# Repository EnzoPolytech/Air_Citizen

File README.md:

# Air_Citizen
Ressources concernant la conception d'un module de capteur de gaz pour le client Air Citizen dans la cadre du Projet Industriel de 4eme année d'EISE de l'école d'ingénieur Polytech Sorbonne

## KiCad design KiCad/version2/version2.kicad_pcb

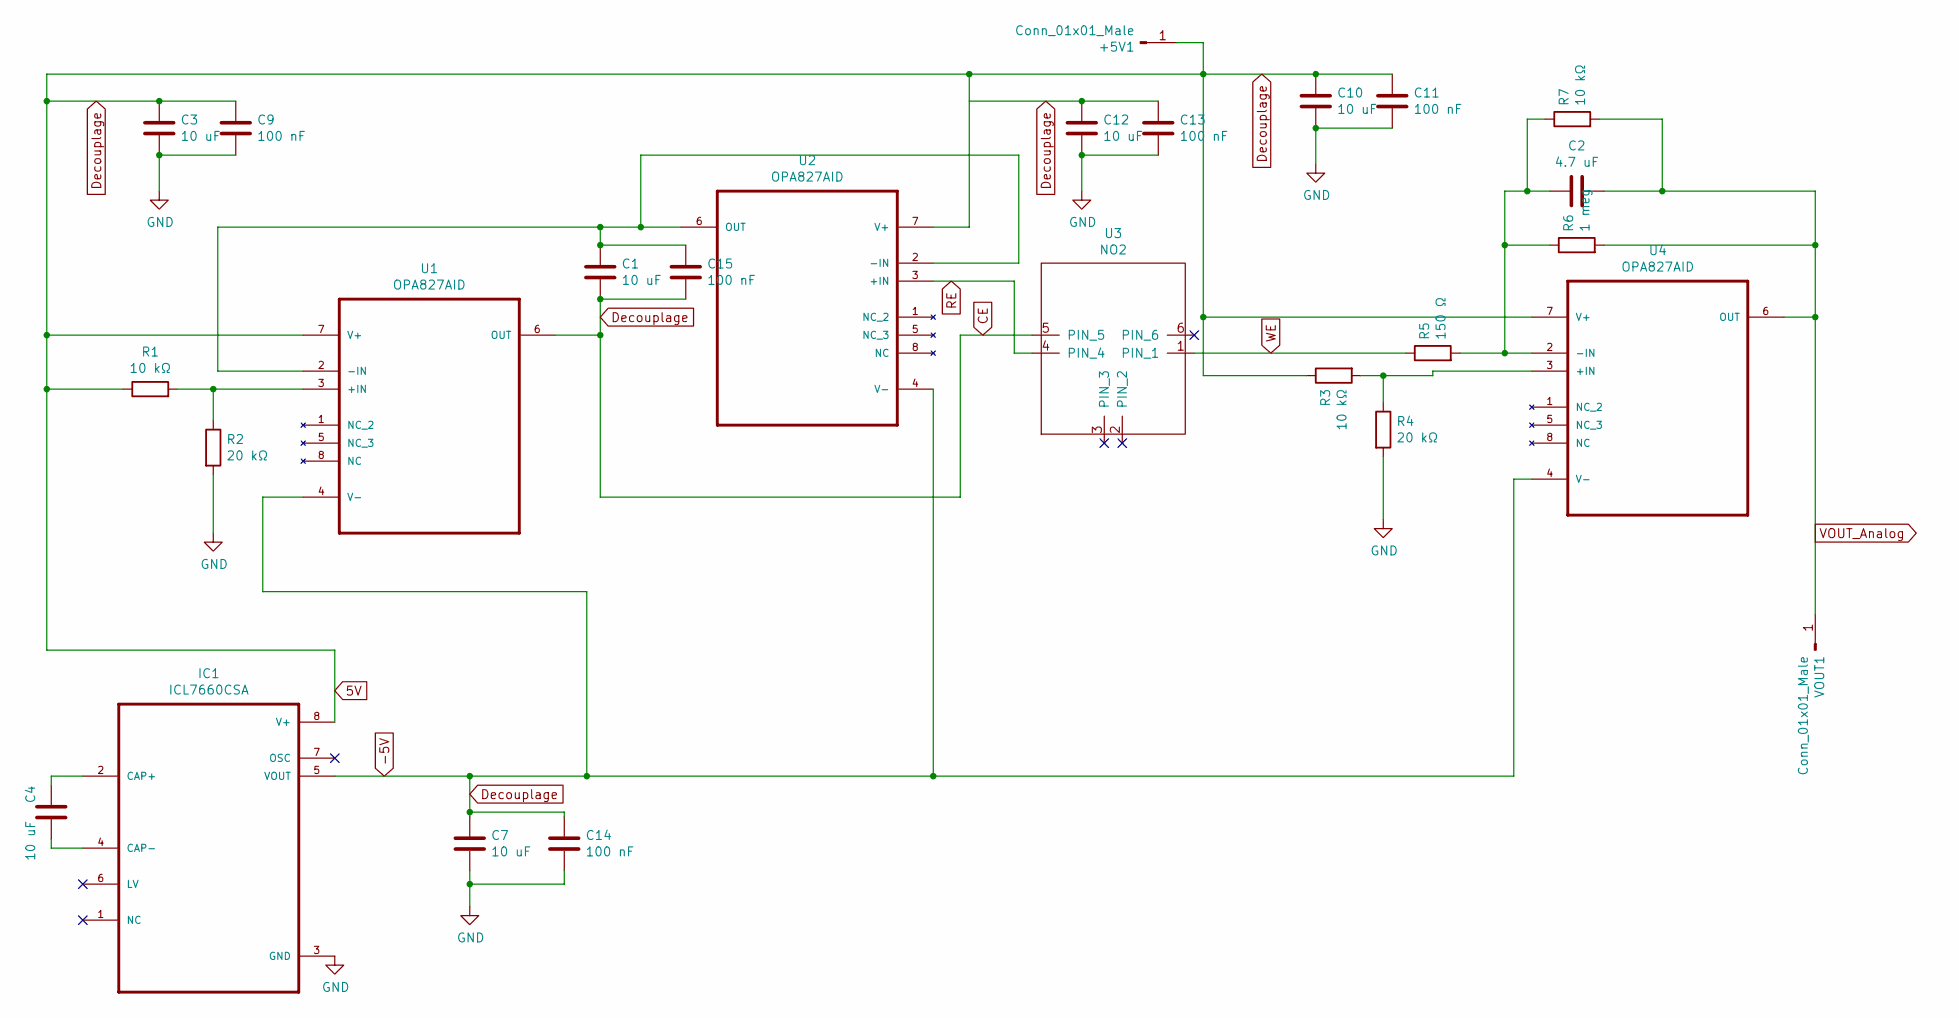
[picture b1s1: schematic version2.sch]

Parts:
+5V1: Conn_01x01_Male; PinHeader_1x01_P2.54mm_Vertical
C1, C3, C4, C7, C10, C12: 10 uF; C_1206_3216Metric
C2: 4.7 uF; C_1206_3216Metric
C9, C11, C13, C14, C15: 100 nF; C_1206_3216Metric
IC1: ICL7660CSA; ICL7600CSA
R1, R3, R7: 10 kΩ; R_0805_2012Metric
R2, R4: 20 kΩ; R_0805_2012Metric
R5: 150 Ω; R_0805_2012Metric
R6: 1 meg; R_0805_2012Metric
U1, U2, U4: OPA827AID; SOIC127P600X175-8N
U3: NO2
VOUT1: Conn_01x01_Male; PinHeader_1x01_P2.54mm_Vertical

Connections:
-5V: +5V1.1, C1.2, C3.1, C7.1, C9.1, C10.1, C11.1, C12.1, C13.1, C14.1, C15.2, IC1.5 (VOUT), IC1.8 (V+), R1.1, R3.1, U1.4 (V-), U1.6 (OUT), U1.7 (V+), U2.4 (V-), U2.7 (V+), U3.5 (PIN_5), U4.4 (V-), U4.7 (V+)
GND: C3.2, C7.2, C9.2, C10.2, C11.2, C12.2, C13.2, C14.2, IC1.3 (GND), R2.2, R4.2; also elsewhere on the board
unnamed: C1.1, C15.1, U1.2 (-IN), U2.2 (-IN), U2.6 (OUT)
unnamed: C2.2, R5.2, R6.1, R7.1, U4.2 (-IN)
unnamed: C4.1, IC1.2 (CAP+)
unnamed: C4.2, IC1.4 (CAP-)
unnamed: R1.2, R2.1, U1.3 (+IN)
unnamed: R3.2, R4.1, U4.3 (+IN)
RE: U2.3 (+IN), U3.4 (PIN_4)
VOUT_Analog: C2.1, R6.2, R7.2, U4.6 (OUT), VOUT1.1
WE: R5.1, U3.1 (PIN_1)

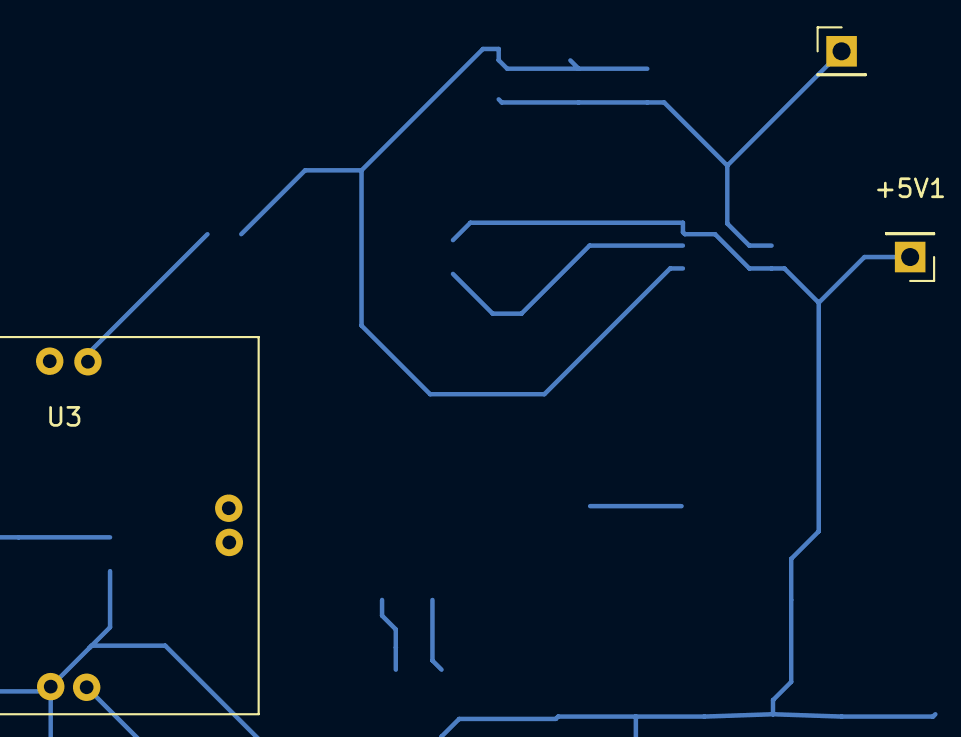
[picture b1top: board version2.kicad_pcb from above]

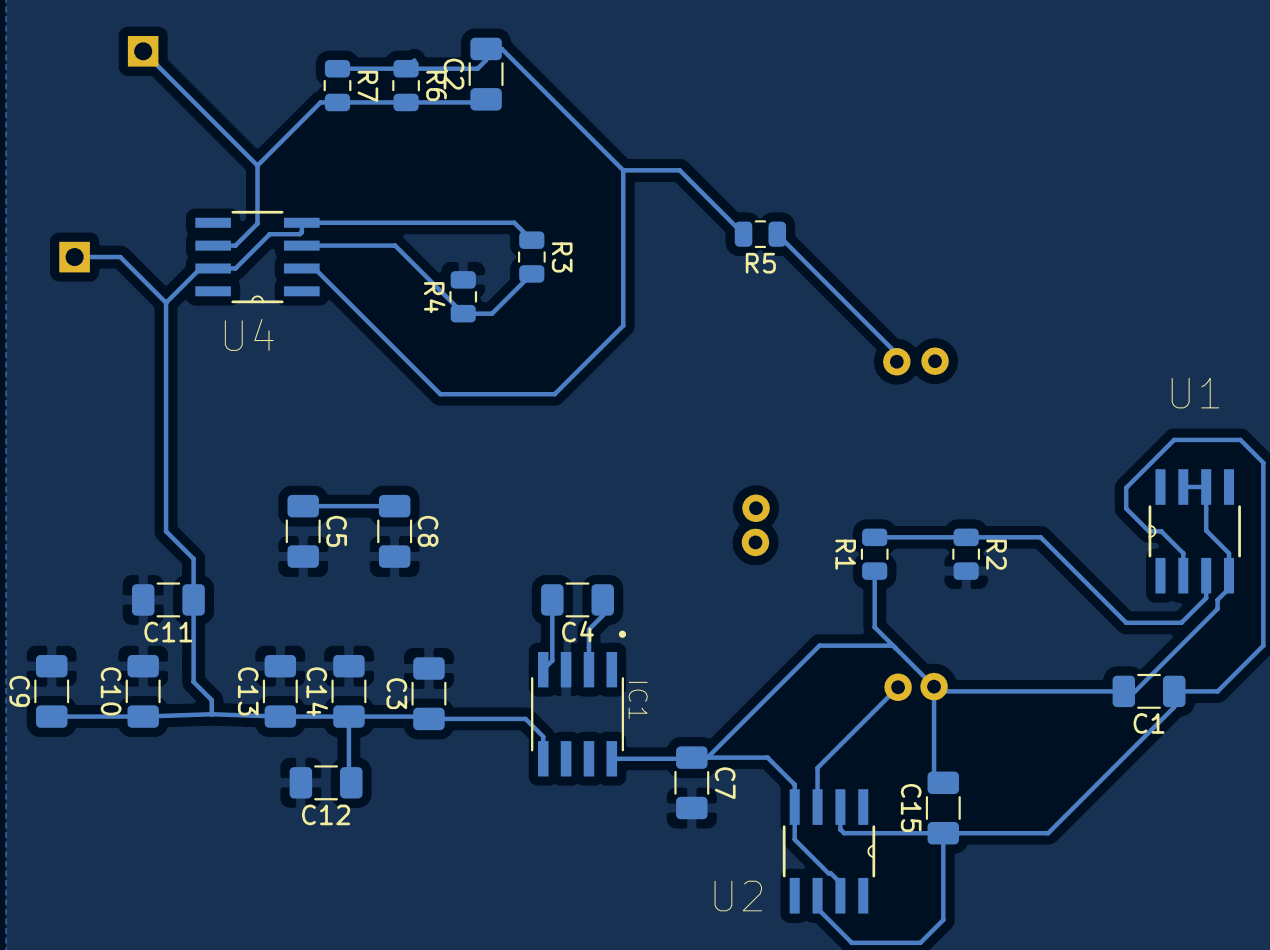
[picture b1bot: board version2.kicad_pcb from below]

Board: 2 copper layers, 28 parts (25 on the bottom side), 12 nets.

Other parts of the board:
C5, C8: C; C_1206_3216Metric

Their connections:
GND: C5.2, C8.2; also elsewhere on the board
unnamed: C5.1, C8.1

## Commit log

2020-05-22 ajout ressources
